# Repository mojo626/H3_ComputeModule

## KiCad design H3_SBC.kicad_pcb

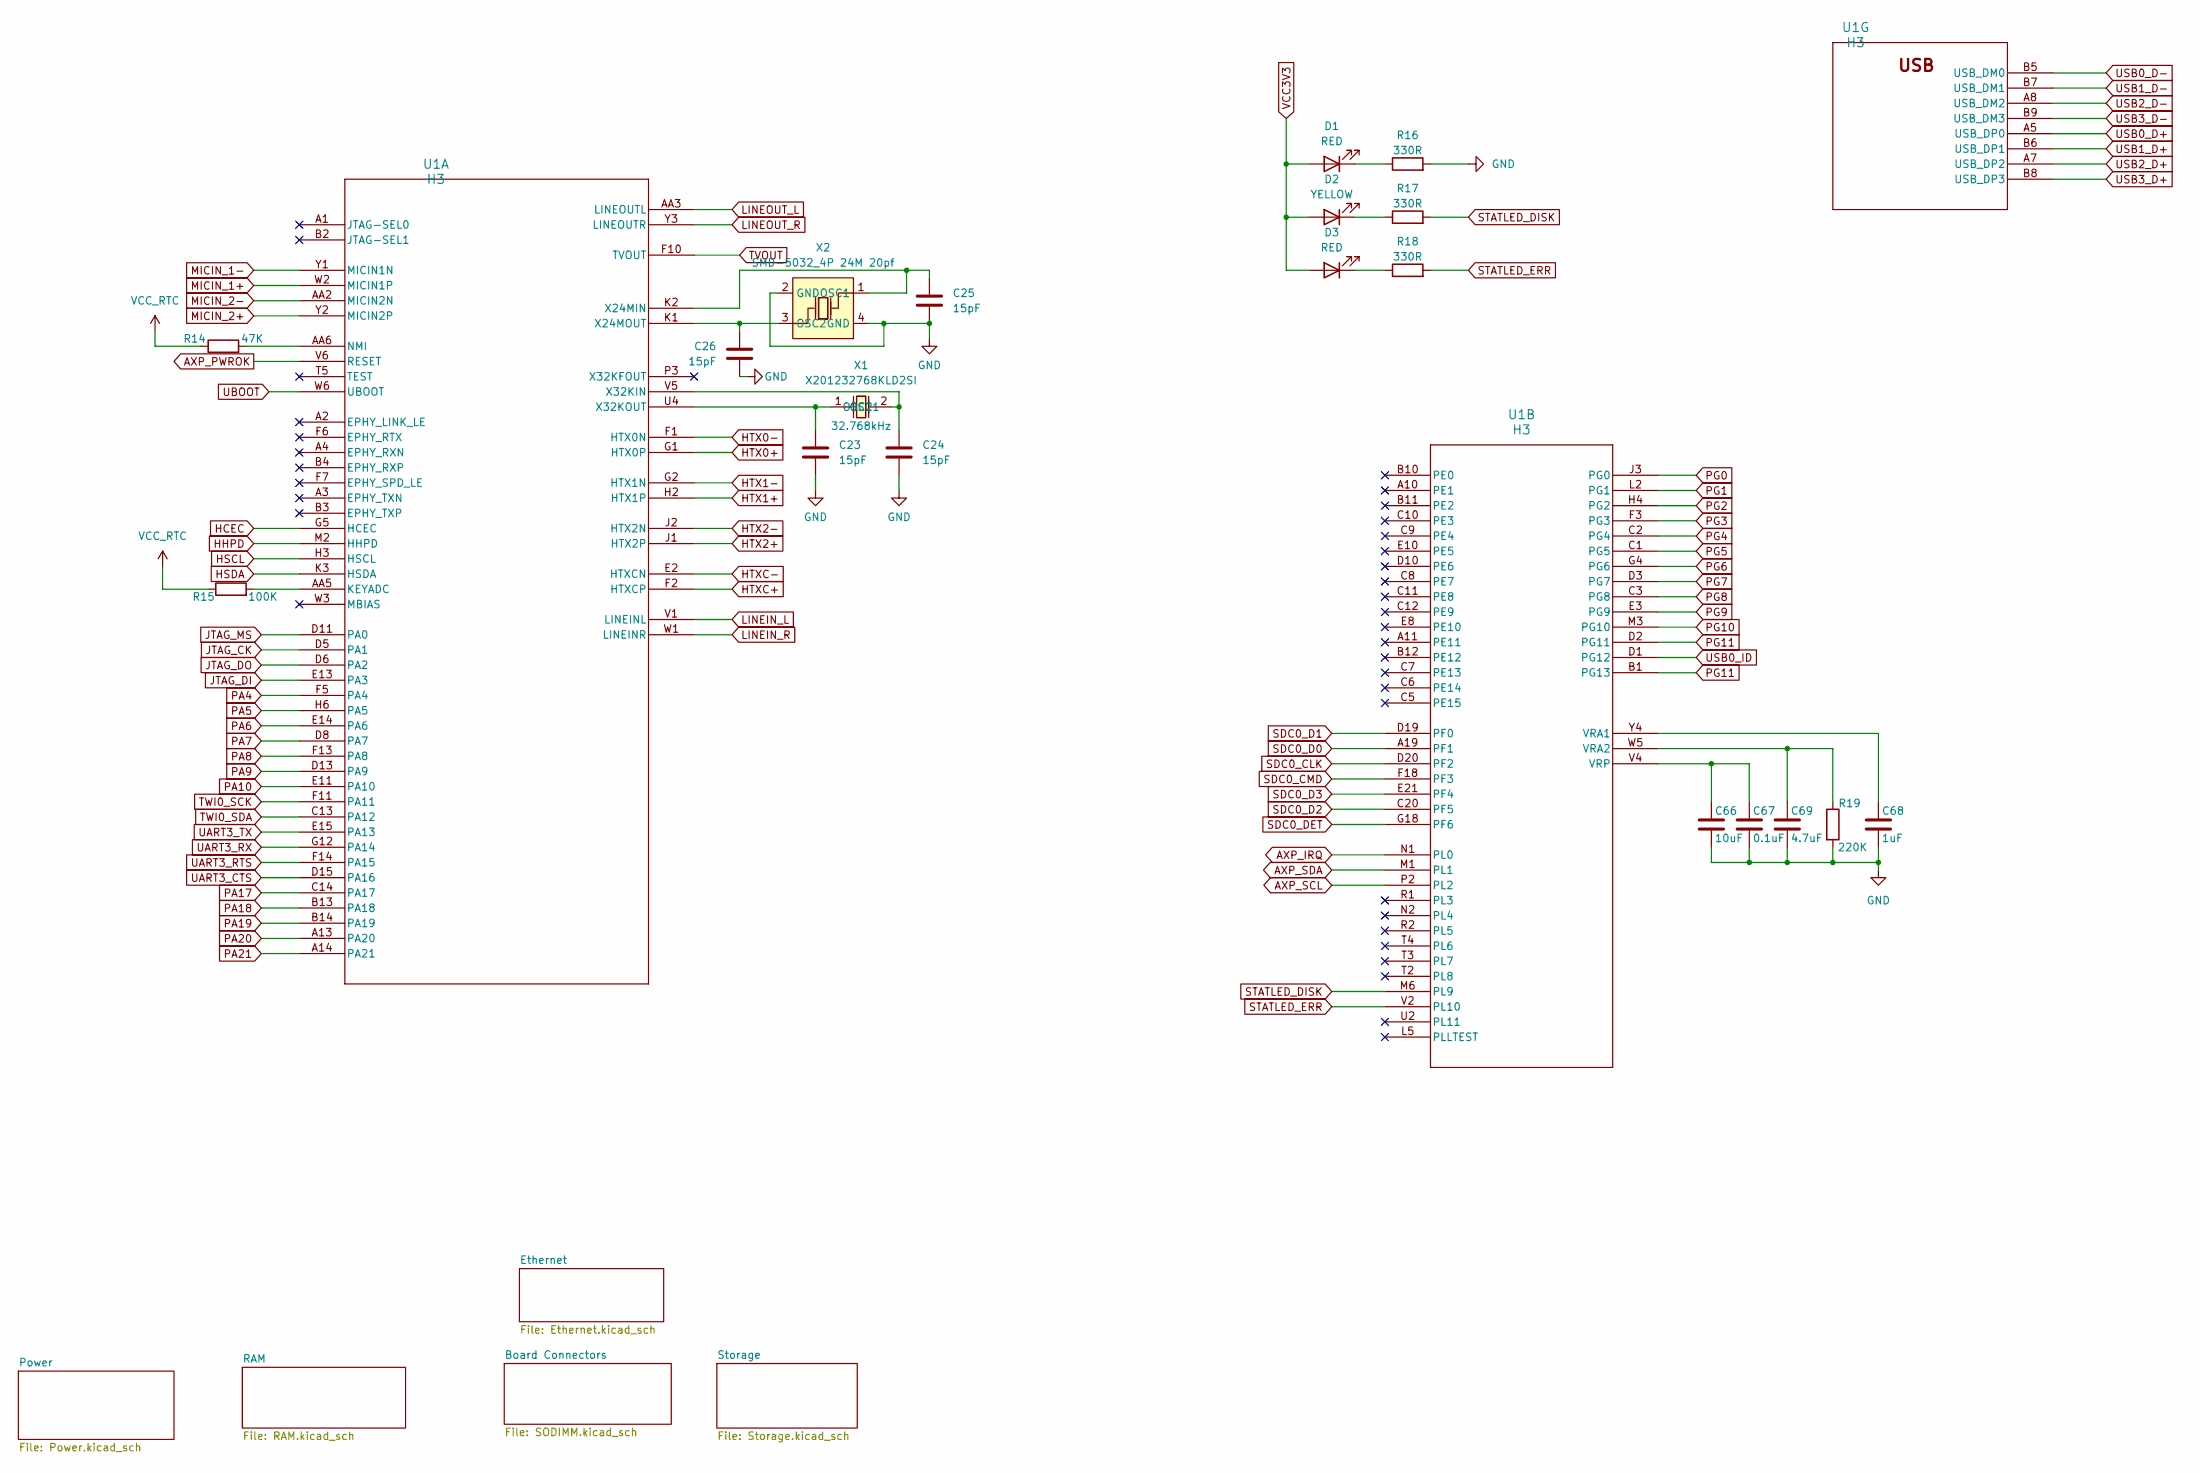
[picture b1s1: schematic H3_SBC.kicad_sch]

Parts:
C23, C24, C25, C26: 15pF; C_0402_1005Metric
C66: 10uF; C_0402_1005Metric
C67: 0.1uF; C_0402_1005Metric
C68: 1uF; C_0402_1005Metric
C69: 4.7uF; C_0402_1005Metric
D1, D3: RED; LED_0402_1005Metric
D2: YELLOW; LED_0402_1005Metric
R14: 47K; R_0402_1005Metric
R15: 100K; R_0402_1005Metric
R16, R17, R18: 330R; R_0402_1005Metric
R19: 220K; R_0402_1005Metric
U1: H3; BGA-347_L14.0-W14.0-R21-C21-P0.65-TL
X1: X201232768KLD2SI; OSC-SMD_L2.0-W1.2; LCSC Part C383842
X2: SMD-5032_4P 24M 20pf; CRYSTAL-SMD_4P-L5.0-W3.2-BL; LCSC Part C362358

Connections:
AXP_IRQ: U1.N1 (PL0); also elsewhere on the board
AXP_PWROK: U1.V6 (RESET); also elsewhere on the board
AXP_SCL: U1.P2 (PL2); also elsewhere on the board
AXP_SDA: U1.M1 (PL1); also elsewhere on the board
GND: C23.2, C24.2, C25.2, C26.2, C66.2, C67.2, C68.2, C69.2, R16.2, R19.2, X2.2 (GND), X2.4 (GND); also elsewhere on the board
HCEC: U1.G5 (HCEC); also elsewhere on the board
HHPD: U1.M2 (HHPD); also elsewhere on the board
HSCL: U1.H3 (HSCL); also elsewhere on the board
HSDA: U1.K3 (HSDA); also elsewhere on the board
HTX0+: U1.G1 (HTX0P); also elsewhere on the board
HTX0-: U1.F1 (HTX0N); also elsewhere on the board
HTX1+: U1.H2 (HTX1P); also elsewhere on the board
HTX1-: U1.G2 (HTX1N); also elsewhere on the board
HTX2+: U1.J1 (HTX2P); also elsewhere on the board
HTX2-: U1.J2 (HTX2N); also elsewhere on the board
HTXC+: U1.F2 (HTXCP); also elsewhere on the board
HTXC-: U1.E2 (HTXCN); also elsewhere on the board
JTAG_CK: U1.D5 (PA1); also elsewhere on the board
JTAG_DI: U1.E13 (PA3); also elsewhere on the board
JTAG_DO: U1.D6 (PA2); also elsewhere on the board
JTAG_MS: U1.D11 (PA0); also elsewhere on the board
LINEIN_L: U1.V1 (LINEINL); also elsewhere on the board
LINEIN_R: U1.W1 (LINEINR); also elsewhere on the board
LINEOUT_L: U1.AA3 (LINEOUTL); also elsewhere on the board
LINEOUT_R: U1.Y3 (LINEOUTR); also elsewhere on the board
MICIN_1+: U1.W2 (MICIN1P); also elsewhere on the board
MICIN_1-: U1.Y1 (MICIN1N); also elsewhere on the board
MICIN_2+: U1.Y2 (MICIN2P); also elsewhere on the board
MICIN_2-: U1.AA2 (MICIN2N); also elsewhere on the board
unnamed: D1.1 (K), R16.1
unnamed: D2.1 (K), R17.1
unnamed: D3.1 (K), R18.1
unnamed: R15.2, U1.AA5 (KEYADC)
unnamed: R14.2, U1.AA6 (NMI)
unnamed: C25.1, U1.K2 (X24MIN), X2.1 (OSC1)
unnamed: C26.1, U1.K1 (X24MOUT), X2.3 (OSC2)
unnamed: C24.1, U1.V5 (X32KIN), X1.2 (OSC2)
unnamed: C23.1, U1.U4 (X32KOUT), X1.1 (OSC1)
unnamed: C68.1, U1.Y4 (VRA1)
unnamed: C69.1, R19.1, U1.W5 (VRA2)
unnamed: C66.1, C67.1, U1.V4 (VRP)
PA4: U1.F5 (PA4); also elsewhere on the board
PA5: U1.H6 (PA5); also elsewhere on the board
PA6: U1.E14 (PA6); also elsewhere on the board
PA7: U1.D8 (PA7); also elsewhere on the board
PA8: U1.F13 (PA8); also elsewhere on the board
PA9: U1.D13 (PA9); also elsewhere on the board
PA10: U1.E11 (PA10); also elsewhere on the board
PA17: U1.C14 (PA17); also elsewhere on the board
PA18: U1.B13 (PA18); also elsewhere on the board
PA19: U1.B14 (PA19); also elsewhere on the board
PA20: U1.A13 (PA20); also elsewhere on the board
PA21: U1.A14 (PA21); also elsewhere on the board
PG0: U1.J3 (PG0); also elsewhere on the board
PG1: U1.L2 (PG1); also elsewhere on the board
PG2: U1.H4 (PG2); also elsewhere on the board
PG3: U1.F3 (PG3); also elsewhere on the board
PG4: U1.C2 (PG4); also elsewhere on the board
PG5: U1.C1 (PG5); also elsewhere on the board
PG6: U1.G4 (PG6); also elsewhere on the board
PG7: U1.D3 (PG7); also elsewhere on the board
PG8: U1.C3 (PG8); also elsewhere on the board
PG9: U1.E3 (PG9); also elsewhere on the board
PG10: U1.M3 (PG10); also elsewhere on the board
PG11: U1.B1 (PG13), U1.D2 (PG11); also elsewhere on the board
SDC0_CLK: U1.D20 (PF2); also elsewhere on the board
SDC0_CMD: U1.F18 (PF3); also elsewhere on the board
SDC0_D0: U1.A19 (PF1); also elsewhere on the board
SDC0_D1: U1.D19 (PF0); also elsewhere on the board
SDC0_D2: U1.C20 (PF5); also elsewhere on the board
SDC0_D3: U1.E21 (PF4); also elsewhere on the board
SDC0_DET: U1.G18 (PF6); also elsewhere on the board
STATLED_DISK: R17.2, U1.M6 (PL9)
STATLED_ERR: R18.2, U1.V2 (PL10)
TVOUT: U1.F10 (TVOUT); also elsewhere on the board
TWI0_SCK: U1.F11 (PA11); also elsewhere on the board
TWI0_SDA: U1.C13 (PA12); also elsewhere on the board
UART3_CTS: U1.D15 (PA16); also elsewhere on the board
UART3_RTS: U1.F14 (PA15); also elsewhere on the board
UART3_RX: U1.G12 (PA14); also elsewhere on the board
UART3_TX: U1.E15 (PA13); also elsewhere on the board
UBOOT: U1.W6 (UBOOT); also elsewhere on the board
USB0_D+: U1.A5 (USB_DP0); also elsewhere on the board
USB0_D-: U1.B5 (USB_DM0); also elsewhere on the board
USB0_ID: U1.D1 (PG12); also elsewhere on the board
USB1_D+: U1.B6 (USB_DP1); also elsewhere on the board
USB1_D-: U1.B7 (USB_DM1); also elsewhere on the board
USB2_D+: U1.A7 (USB_DP2); also elsewhere on the board
USB2_D-: U1.A8 (USB_DM2); also elsewhere on the board
USB3_D+: U1.B8 (USB_DP3); also elsewhere on the board
USB3_D-: U1.B9 (USB_DM3); also elsewhere on the board
VCC3V3: D1.2 (A), D2.2 (A), D3.2 (A); also elsewhere on the board
VCC_RTC: R14.1, R15.1; also elsewhere on the board

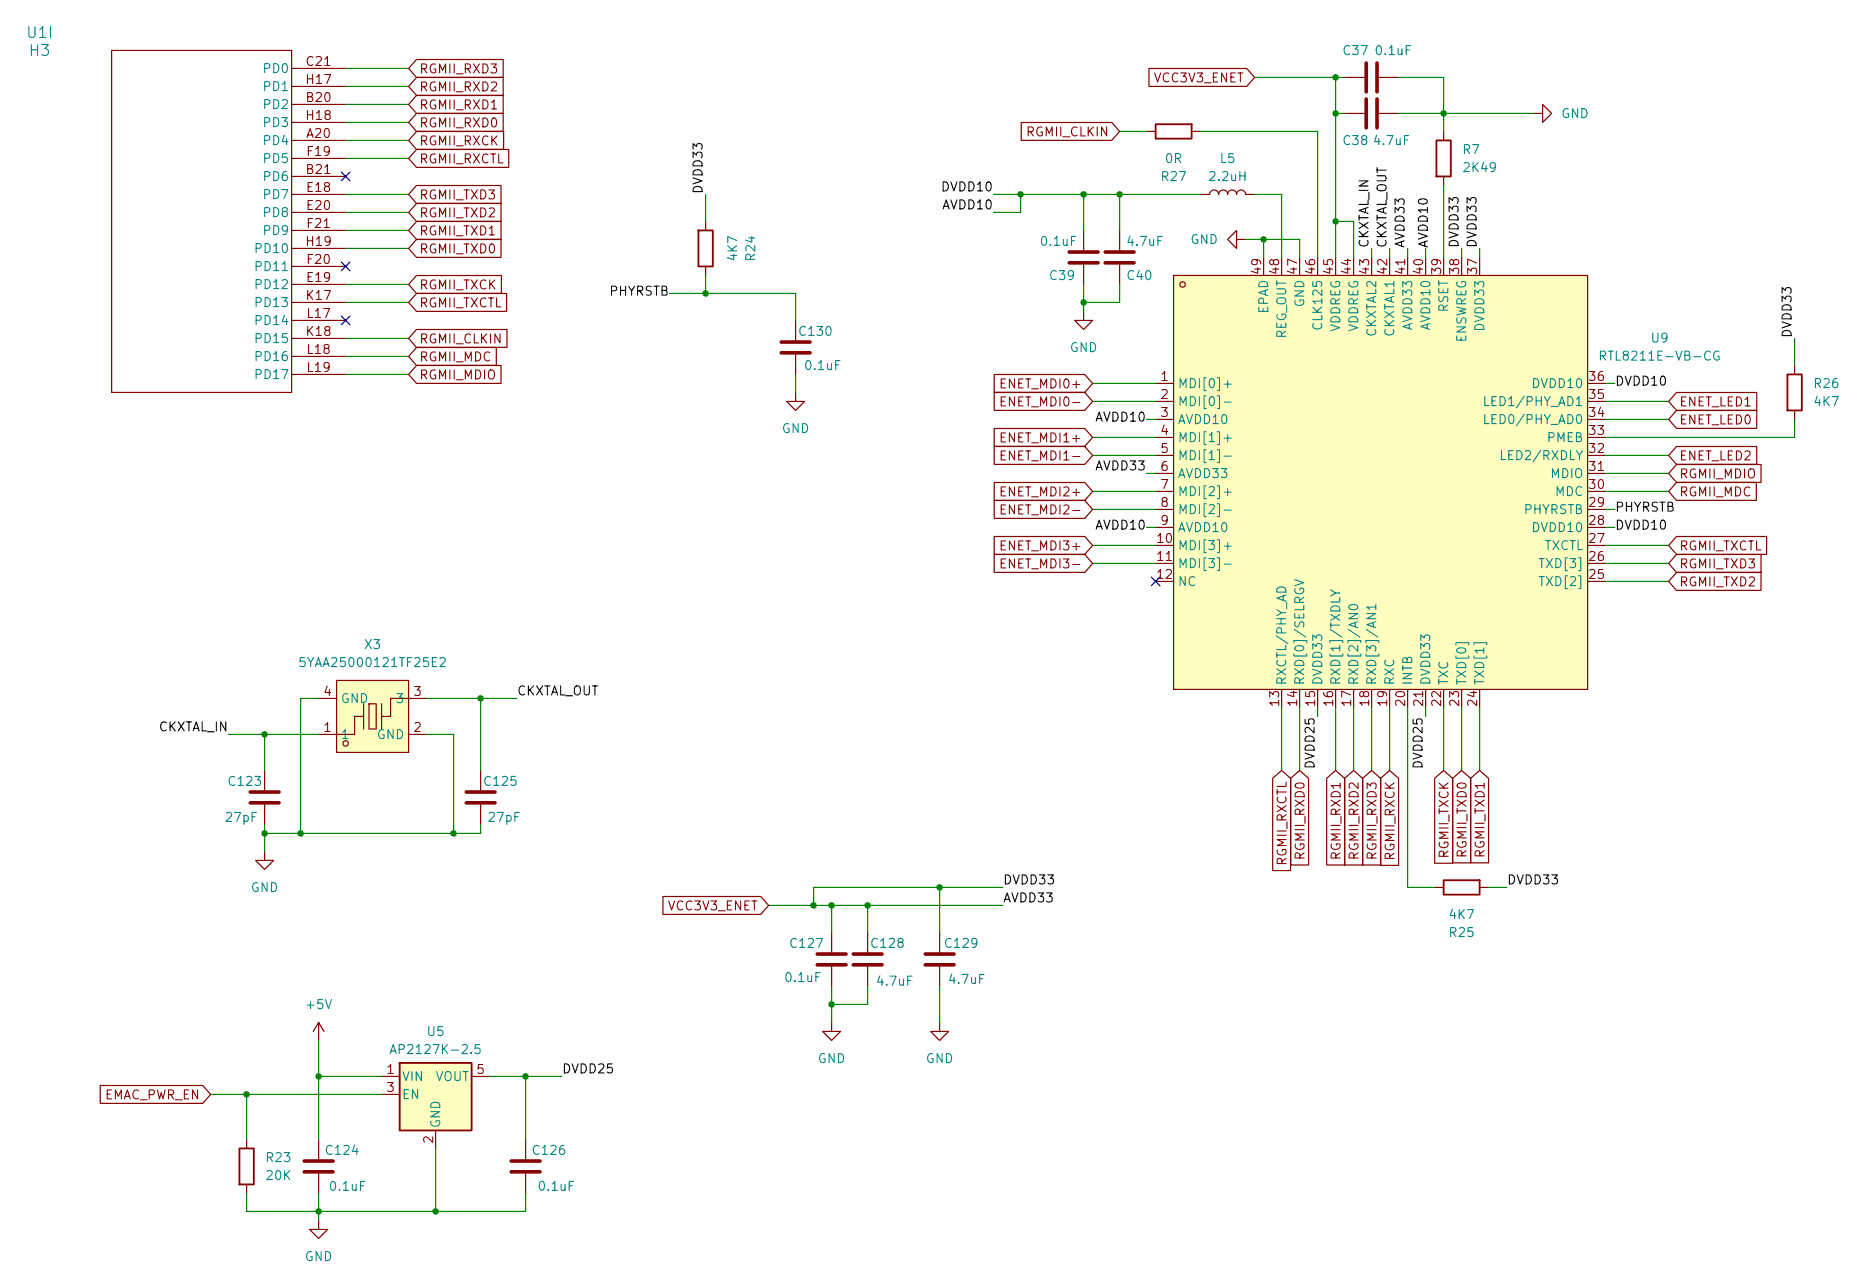
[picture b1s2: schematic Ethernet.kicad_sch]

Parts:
C37, C39, C124, C126, C127, C130: 0.1uF; C_0402_1005Metric
C38, C40, C128, C129: 4.7uF; C_0402_1005Metric
C123, C125: 27pF; C_0402_1005Metric
L5: 2.2uH; L_0402_1005Metric
R7: 2K49; R_0402_1005Metric
R23: 20K; R_0402_1005Metric
R24, R25, R26: 4K7; R_0402_1005Metric
R27: 0R; R_0402_1005Metric
U1: H3; BGA-347_L14.0-W14.0-R21-C21-P0.65-TL
U5: AP2127K-2.5; SOT-23-5
U9: RTL8211E-VB-CG; QFN-48_L6.0-W6.0-P0.40-BL-EP3.8; LCSC Part C90735
X3: 5YAA25000121TF25E2; CRYSTAL-SMD_4P-L3.2-W2.5-BL; LCSC Part C3003239

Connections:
+5V: C124.2, U5.1 (VIN); also elsewhere on the board
/Ethernet/AVDD10: C39.2, C40.2, L5.1, U9.3 (AVDD10), U9.9 (AVDD10), U9.28 (DVDD10), U9.36 (DVDD10), U9.40 (AVDD10)
/Ethernet/CKXTAL_IN: C123.2, U9.43 (CKXTAL2), X3.1
/Ethernet/CKXTAL_OUT: C125.2, U9.42 (CKXTAL1), X3.3
/Ethernet/DVDD25: C126.2, U5.5 (VOUT), U9.15 (DVDD33), U9.21 (DVDD33)
/Ethernet/PHYRSTB: C130.2, R24.1, U9.29 (PHYRSTB)
EMAC_PWR_EN: R23.1, U5.3 (EN)
ENET_LED0: U9.34 (LED0/PHY_AD0); also elsewhere on the board
ENET_LED1: U9.35 (LED1/PHY_AD1); also elsewhere on the board
ENET_LED2: U9.32 (LED2/RXDLY); also elsewhere on the board
ENET_MDI0+: U9.1 (MDI[0]+); also elsewhere on the board
ENET_MDI0-: U9.2 (MDI[0]-); also elsewhere on the board
ENET_MDI1+: U9.4 (MDI[1]+); also elsewhere on the board
ENET_MDI1-: U9.5 (MDI[1]-); also elsewhere on the board
ENET_MDI2+: U9.7 (MDI[2]+); also elsewhere on the board
ENET_MDI2-: U9.8 (MDI[2]-); also elsewhere on the board
ENET_MDI3+: U9.10 (MDI[3]+); also elsewhere on the board
ENET_MDI3-: U9.11 (MDI[3]-); also elsewhere on the board
GND: C37.2, C38.2, C39.1, C40.1, C123.1, C124.1, C125.1, C126.1, C127.1, C128.1, C129.1, C130.1, R7.1, R23.2, U5.2 (GND), U9.47 (GND), U9.49 (EPAD), X3.2 (GND), X3.4 (GND); also elsewhere on the board
unnamed: R27.2, U9.46 (CLK125)
unnamed: R25.1, U9.20 (INTB)
unnamed: R26.2, U9.33 (PMEB)
unnamed: L5.2, U9.48 (REG_OUT)
unnamed: R7.2, U9.39 (RSET)
RGMII_CLKIN: R27.1, U1.K18 (PD15)
RGMII_MDC: U1.L18 (PD16), U9.30 (MDC)
RGMII_MDIO: U1.L19 (PD17), U9.31 (MDIO)
RGMII_RXCK: U1.A20 (PD4), U9.19 (RXC)
RGMII_RXCTL: U1.F19 (PD5), U9.13 (RXCTL/PHY_AD)
RGMII_RXD0: U1.H18 (PD3), U9.14 (RXD[0]/SELRGV)
RGMII_RXD1: U1.B20 (PD2), U9.16 (RXD[1]/TXDLY)
RGMII_RXD2: U1.H17 (PD1), U9.17 (RXD[2]/AN0)
RGMII_RXD3: U1.C21 (PD0), U9.18 (RXD[3]/AN1)
RGMII_TXCK: U1.E19 (PD12), U9.22 (TXC)
RGMII_TXCTL: U1.K17 (PD13), U9.27 (TXCTL)
RGMII_TXD0: U1.H19 (PD10), U9.23 (TXD[0])
RGMII_TXD1: U1.F21 (PD9), U9.24 (TXD[1])
RGMII_TXD2: U1.E20 (PD8), U9.25 (TXD[2])
RGMII_TXD3: U1.E18 (PD7), U9.26 (TXD[3])
VCC3V3: C37.1, C38.1, C127.2, C128.2, C129.2, R24.2, R25.2, R26.1, U9.6 (AVDD33), U9.37 (DVDD33), U9.38 (ENSWREG), U9.41 (AVDD33), U9.44 (VDDREG), U9.45 (VDDREG); also elsewhere on the board

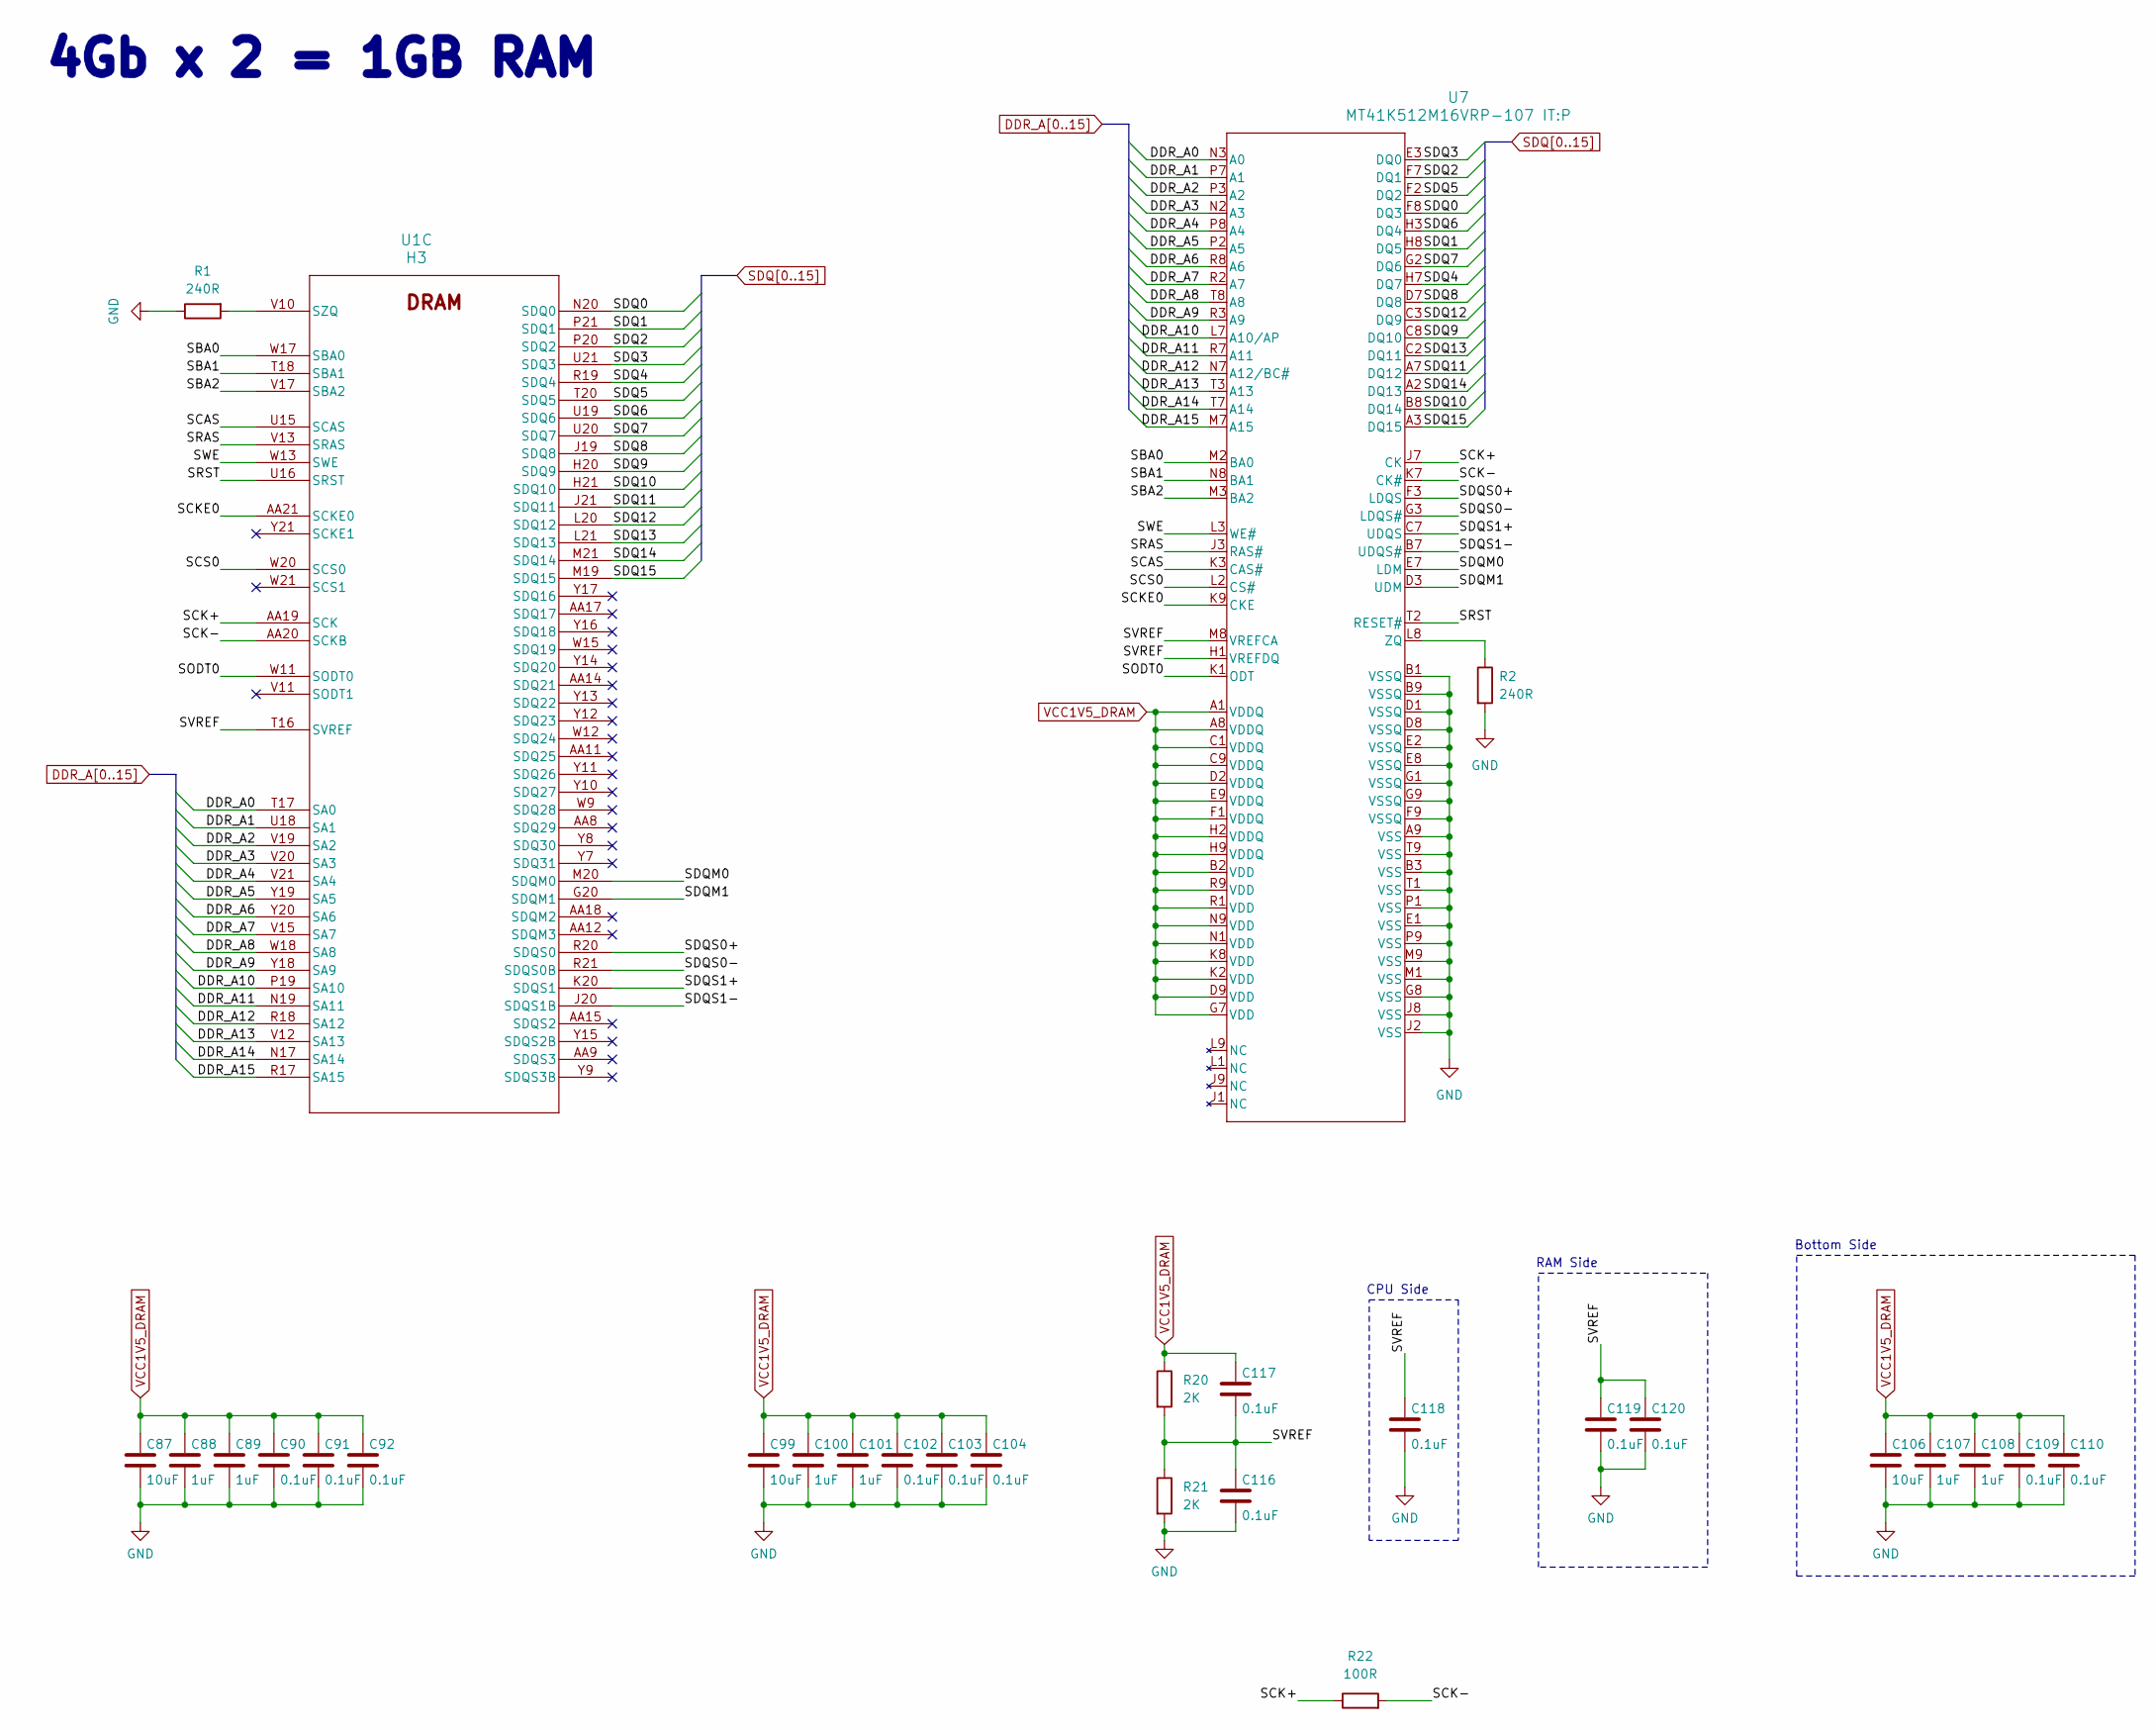
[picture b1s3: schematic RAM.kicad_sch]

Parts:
C87, C99, C106: 10uF; C_0402_1005Metric
C88, C89, C100, C101, C107, C108: 1uF; C_0402_1005Metric
C90, C91, C92, C102, C103, C104, C109, C110, C116, C117, C118, C119, C120: 0.1uF; C_0402_1005Metric
R1, R2: 240R; R_0402_1005Metric
R20, R21: 2K; R_0402_1005Metric
R22: 100R; R_0402_1005Metric
U1: H3; BGA-347_L14.0-W14.0-R21-C21-P0.65-TL
U7: MT41K512M16VRP-107 IT:P; FBGA96_MRN

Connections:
/RAM/SBA0: U1.W17 (SBA0), U7.M2 (BA0)
/RAM/SBA1: U1.T18 (SBA1), U7.N8 (BA1)
/RAM/SBA2: U1.V17 (SBA2), U7.M3 (BA2)
/RAM/SCAS: U1.U15 (SCAS), U7.K3 (CAS#)
/RAM/SCK+: R22.1, U1.AA19 (SCK), U7.J7 (CK)
/RAM/SCK-: R22.2, U1.AA20 (SCKB), U7.K7 (CK#)
/RAM/SCKE0: U1.AA21 (SCKE0), U7.K9 (CKE)
/RAM/SCS0: U1.W20 (SCS0), U7.L2 (CS#)
/RAM/SDQM0: U1.M20 (SDQM0), U7.E7 (LDM)
/RAM/SDQM1: U1.G20 (SDQM1), U7.D3 (UDM)
/RAM/SDQS0+: U1.R20 (SDQS0), U7.F3 (LDQS)
/RAM/SDQS0-: U1.R21 (SDQS0B), U7.G3 (LDQS#)
/RAM/SDQS1+: U1.K20 (SDQS1), U7.C7 (UDQS)
/RAM/SDQS1-: U1.J20 (SDQS1B), U7.B7 (UDQS#)
/RAM/SODT0: U1.W11 (SODT0), U7.K1 (ODT)
/RAM/SRAS: U1.V13 (SRAS), U7.J3 (RAS#)
/RAM/SRST: U1.U16 (SRST), U7.T2 (RESET#)
/RAM/SVREF: C116.1, C117.2, C118.1, C119.1, C120.1, R20.2, R21.1, U1.T16 (SVREF), U7.H1 (VREFDQ), U7.M8 (VREFCA)
/RAM/SWE: U1.W13 (SWE), U7.L3 (WE#)
DDR_A0: U1.T17 (SA0), U7.N3 (A0)
DDR_A1: U1.U18 (SA1), U7.P7 (A1)
DDR_A2: U1.V19 (SA2), U7.P3 (A2)
DDR_A3: U1.V20 (SA3), U7.N2 (A3)
DDR_A4: U1.V21 (SA4), U7.P8 (A4)
DDR_A5: U1.Y19 (SA5), U7.P2 (A5)
DDR_A6: U1.Y20 (SA6), U7.R8 (A6)
DDR_A7: U1.V15 (SA7), U7.R2 (A7)
DDR_A8: U1.W18 (SA8), U7.T8 (A8)
DDR_A9: U1.Y18 (SA9), U7.R3 (A9)
DDR_A10: U1.P19 (SA10), U7.L7 (A10/AP)
DDR_A11: U1.N19 (SA11), U7.R7 (A11)
DDR_A12: U1.R18 (SA12), U7.N7 (A12/BC#)
DDR_A13: U1.V12 (SA13), U7.T3 (A13)
DDR_A14: U1.N17 (SA14), U7.T7 (A14)
DDR_A15: U1.R17 (SA15), U7.M7 (A15)
GND: C87.2, C88.2, C89.2, C90.2, C91.2, C92.2, C99.2, C100.2, C101.2, C102.2, C103.2, C104.2, C106.2, C107.2, C108.2, C109.2, C110.2, C116.2, C118.2, C119.2, C120.2, R1.1, R2.2, R21.2, U7.A9 (VSS), U7.B1 (VSSQ), U7.B3 (VSS), U7.B9 (VSSQ), U7.D1 (VSSQ), U7.D8 (VSSQ), U7.E1 (VSS), U7.E2 (VSSQ), U7.E8 (VSSQ), U7.F9 (VSSQ), U7.G1 (VSSQ), U7.G8 (VSS), U7.G9 (VSSQ), U7.J2 (VSS), U7.J8 (VSS), U7.M1 (VSS), U7.M9 (VSS), U7.P1 (VSS), U7.P9 (VSS), U7.T1 (VSS), U7.T9 (VSS); also elsewhere on the board
unnamed: R1.2, U1.V10 (SZQ)
unnamed: R2.1, U7.L8 (ZQ)
SDQ0: U1.N20 (SDQ0), U7.F8 (DQ3)
SDQ1: U1.P21 (SDQ1), U7.H8 (DQ5)
SDQ2: U1.P20 (SDQ2), U7.F7 (DQ1)
SDQ3: U1.U21 (SDQ3), U7.E3 (DQ0)
SDQ4: U1.R19 (SDQ4), U7.H7 (DQ7)
SDQ5: U1.T20 (SDQ5), U7.F2 (DQ2)
SDQ6: U1.U19 (SDQ6), U7.H3 (DQ4)
SDQ7: U1.U20 (SDQ7), U7.G2 (DQ6)
SDQ8: U1.J19 (SDQ8), U7.D7 (DQ8)
SDQ9: U1.H20 (SDQ9), U7.C8 (DQ10)
SDQ10: U1.H21 (SDQ10), U7.B8 (DQ14)
SDQ11: U1.J21 (SDQ11), U7.A7 (DQ12)
SDQ12: U1.L20 (SDQ12), U7.C3 (DQ9)
SDQ13: U1.L21 (SDQ13), U7.C2 (DQ11)
SDQ14: U1.M21 (SDQ14), U7.A2 (DQ13)
SDQ15: U1.M19 (SDQ15), U7.A3 (DQ15)
VCC1V5_DRAM: C87.1, C88.1, C89.1, C90.1, C91.1, C92.1, C99.1, C100.1, C101.1, C102.1, C103.1, C104.1, C106.1, C107.1, C108.1, C109.1, C110.1, C117.1, R20.1, U7.A1 (VDDQ), U7.A8 (VDDQ), U7.B2 (VDD), U7.C1 (VDDQ), U7.C9 (VDDQ), U7.D2 (VDDQ), U7.D9 (VDD), U7.E9 (VDDQ), U7.F1 (VDDQ), U7.G7 (VDD), U7.H2 (VDDQ), U7.H9 (VDDQ), U7.K2 (VDD), U7.K8 (VDD), U7.N1 (VDD), U7.N9 (VDD), U7.R1 (VDD), U7.R9 (VDD); also elsewhere on the board

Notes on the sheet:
RAM Side
Bottom Side
4Gb x 2 = 1GB RAM
CPU Side

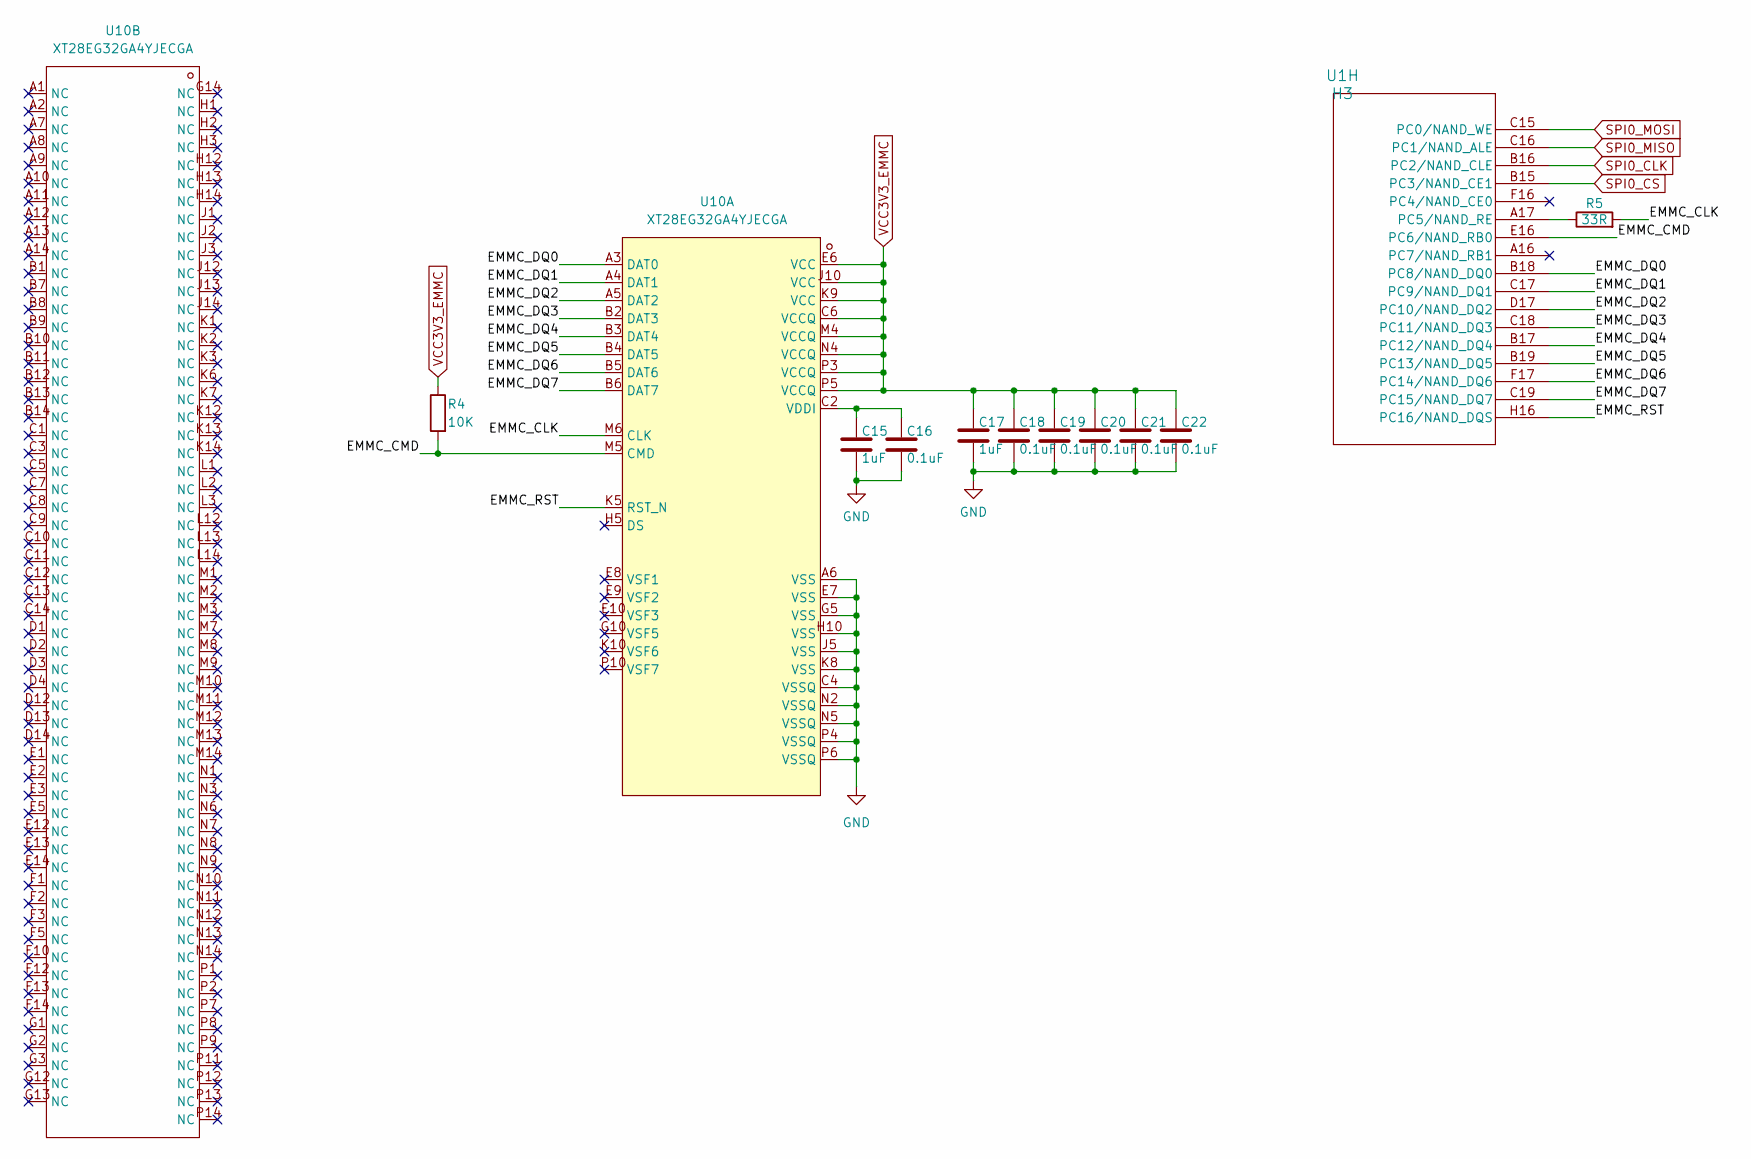
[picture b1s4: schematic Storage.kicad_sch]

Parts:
C15, C17: 1uF; C_0402_1005Metric
C16, C18, C19, C20, C21, C22: 0.1uF; C_0402_1005Metric
R4: 10K; R_0402_1005Metric
R5: 33R; R_0402_1005Metric
U1: H3; BGA-347_L14.0-W14.0-R21-C21-P0.65-TL
U10: XT28EG32GA4YJECGA; VFBGA-153_L13.0-W11.5-P0.50-BL_SKYHIGHMEMORY_S40FC004C1B1I0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; LCSC Part C29781620

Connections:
/Storage/EMMC_CLK: R5.2, U10.M6 (CLK)
/Storage/EMMC_CMD: R4.2, U1.E16 (PC6/NAND_RB0), U10.M5 (CMD)
/Storage/EMMC_DQ0: U1.B18 (PC8/NAND_DQ0), U10.A3 (DAT0)
/Storage/EMMC_DQ1: U1.C17 (PC9/NAND_DQ1), U10.A4 (DAT1)
/Storage/EMMC_DQ2: U1.D17 (PC10/NAND_DQ2), U10.A5 (DAT2)
/Storage/EMMC_DQ3: U1.C18 (PC11/NAND_DQ3), U10.B2 (DAT3)
/Storage/EMMC_DQ4: U1.B17 (PC12/NAND_DQ4), U10.B3 (DAT4)
/Storage/EMMC_DQ5: U1.B19 (PC13/NAND_DQ5), U10.B4 (DAT5)
/Storage/EMMC_DQ6: U1.F17 (PC14/NAND_DQ6), U10.B5 (DAT6)
/Storage/EMMC_DQ7: U1.C19 (PC15/NAND_DQ7), U10.B6 (DAT7)
/Storage/EMMC_RST: U1.H16 (PC16/NAND_DQS), U10.K5 (RST_N)
GND: C15.2, C16.2, C17.2, C18.2, C19.2, C20.2, C21.2, C22.2, U10.A6 (VSS), U10.C4 (VSSQ), U10.E7 (VSS), U10.G5 (VSS), U10.H10 (VSS), U10.J5 (VSS), U10.K8 (VSS), U10.N2 (VSSQ), U10.N5 (VSSQ), U10.P4 (VSSQ), U10.P6 (VSSQ); also elsewhere on the board
unnamed: R5.1, U1.A17 (PC5/NAND_RE)
unnamed: C15.1, C16.1, U10.C2 (VDDI)
SPI0_CLK: U1.B16 (PC2/NAND_CLE); also elsewhere on the board
SPI0_CS: U1.B15 (PC3/NAND_CE1); also elsewhere on the board
SPI0_MISO: U1.C16 (PC1/NAND_ALE); also elsewhere on the board
SPI0_MOSI: U1.C15 (PC0/NAND_WE); also elsewhere on the board
VCC3V3: C17.1, C18.1, C19.1, C20.1, C21.1, C22.1, R4.1, U10.C6 (VCCQ), U10.E6 (VCC), U10.J10 (VCC), U10.K9 (VCC), U10.M4 (VCCQ), U10.N4 (VCCQ), U10.P3 (VCCQ), U10.P5 (VCCQ); also elsewhere on the board
